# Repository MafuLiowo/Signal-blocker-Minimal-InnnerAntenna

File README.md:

# Signal-blocker-Minimal-InnnerAntenna
As it is named!

物如其名

物は名の通り

InnerAntenna version is now available!

PCB board!

How to use: the BOM excel includes all the things you need.

The release file is the file you need to hand in to the PCB manufaturer.

Like JLCPCB,Foxconn,SCC,TTM Technologies.

It may cost some fee.

Language support:

简体中文 日本語 English

VCO module can be replaced to anyother VCO module to block any frequence!

recommended:GSM/CDMA TD-LTE MICROWAVE

Thank you for your star!

给颗星星谢谢啦！

ありがとうございます

( '﹃'⑉)

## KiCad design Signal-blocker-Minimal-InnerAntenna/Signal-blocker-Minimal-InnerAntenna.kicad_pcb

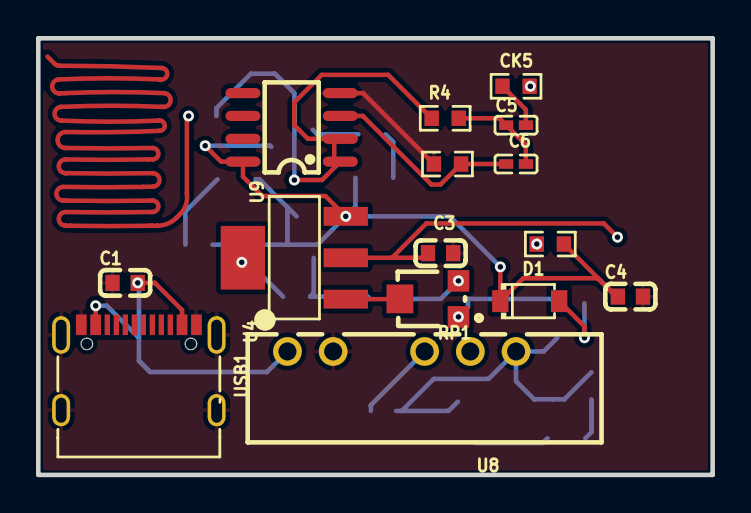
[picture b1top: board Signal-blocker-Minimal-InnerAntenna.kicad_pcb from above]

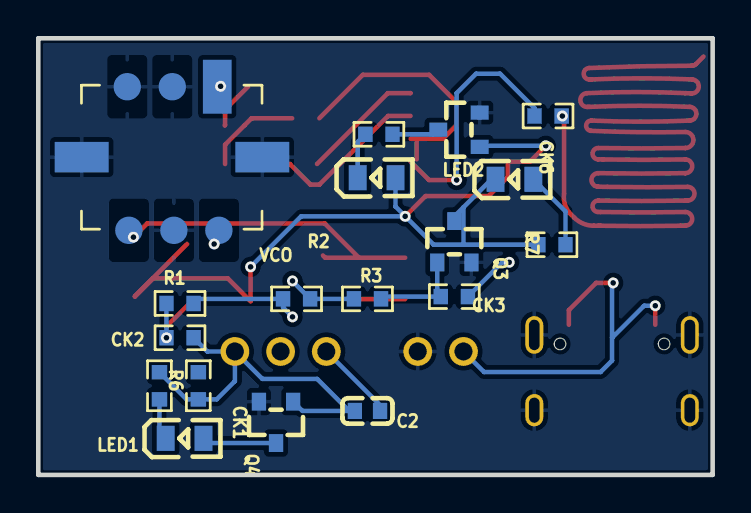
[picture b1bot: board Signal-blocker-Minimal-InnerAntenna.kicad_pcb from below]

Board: 2 copper layers, 37.5 x 24.3 mm, 33 parts (18 on the bottom side), 15 nets.

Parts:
C1, C2, C3, C4: C0603
C5, C6: C0402
CK1, CK2, CK3, CK4, CK5, CK6: R0603
D1: SOD-123_L2.7-W1.6-LS3.7-RD
LED1, LED2, LED2#2: LED0805-R-RD
Q3, Q3#2, Q4: S8050_SOT-23
R1, R2, R3, R4, R5, R6, R6#2, R7: R0603
RP1: RES-ADJ-SMD_3P-L3.0-W3.8-P1.75-BR
U4: SOT-223_L6.3-W3.5-P2.30-LS7.0-BR
U8: PWRM-TH_A05XXS-1WR3
U9: SOIC-8_L5.0-W4.0-P1.27-LS6.0-BL
USB1: TYPE-C-SMD_HDGC_TYPE-C-ZL-104PWB
VCO: 1234

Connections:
$4N521: R2.1, R3.1, RP1.3
$4N526: CK3.2, Q3#2.1, R1.2, R2.2, R3.2, RP1.1
$4N812: CK3.1, U4.4
$5N863: LED2.2, LED2#2.1, R6#2.2, R7.2
$6N289: C5.2, C6.1, CK5.2, R5.2, U9.3
$6N676: C5.1, C6.2, R4.1
ADJ: RP1.2, U4.1
GND: C1.1, C3.1, C4.2, Q3.2, Q3#2.2, Q4.2, R5.1, U8.2, U9.4, USB1.12, USB1.13, USB1.14, USB1.15, USB1.A1B12, USB1.A12B1, VCO.2, VCO.4, VCO.5, VCO.7, VCO.8
POWER: C1.2, U8.1, USB1.A4B9, USB1.A9B4
RFOUT: CK6.1, R4.2, U9.1, U9.2
SIGNAL: CK5.1, VCO.6
VCC9V+: C2.2, CK1.1, CK1.2, CK2.1, LED1.1, LED1.2, Q4.1, Q4.3, R6.1, R6.2, U8.6
VCC+: C4.1, CK2.2, CK4.1, CK4.2, D1.1, D1.2, LED2.1, LED2#2.2, Q3.1, Q3.3, Q3#2.3, R1.1, R6#2.1, R7.1, U4.3, U9.8, VCO.1
VCC-: C2.1, U8.4
VT: C3.2, U4.2, VCO.3

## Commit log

2025-02-27 Inner Antenna!
    The Inner Antenna version of Signal-blocker-Minimal！
    わわわわわわわ
    哇哇哇哇哇哇哇
    Awesome!
2025-02-27 Inner Antenna!
